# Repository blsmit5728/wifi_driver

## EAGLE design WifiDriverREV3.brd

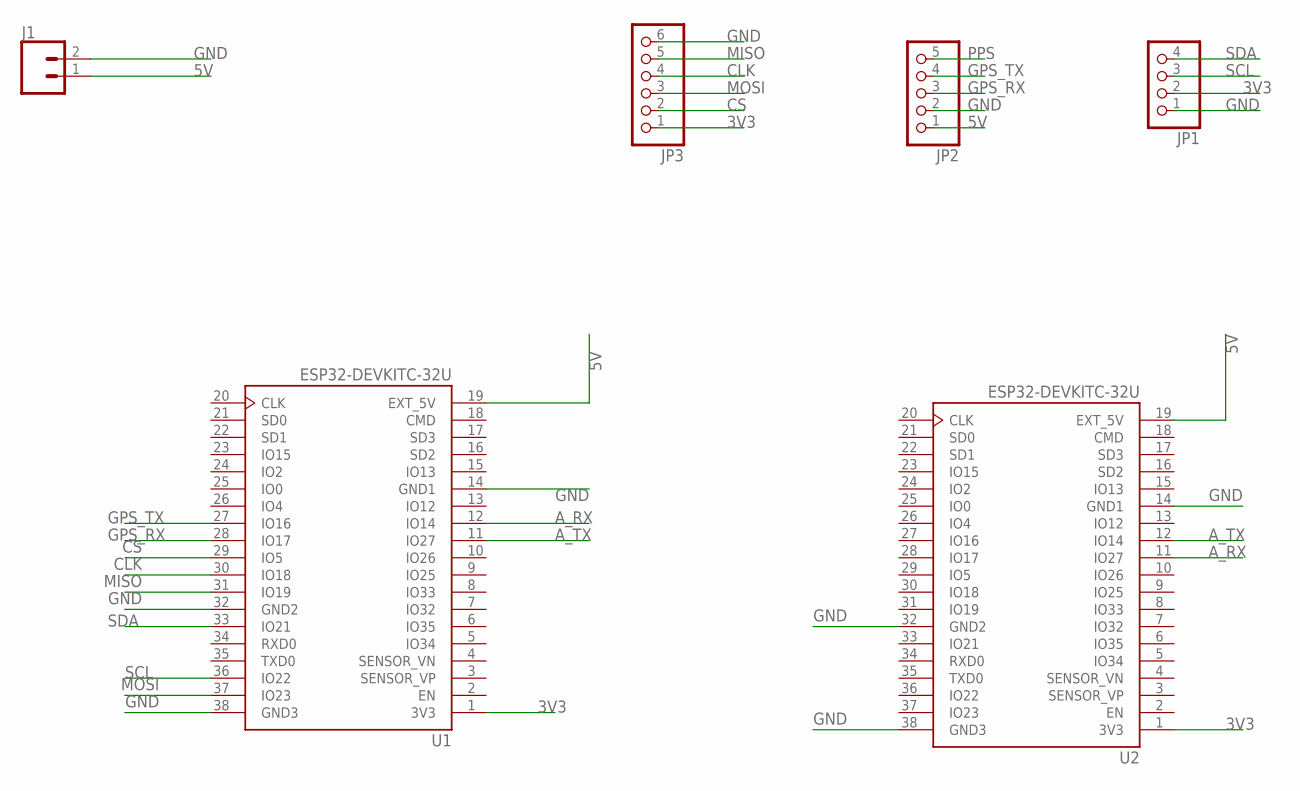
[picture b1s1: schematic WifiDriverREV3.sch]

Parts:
J1: CONN_023.5MM_LOCK; SCREWTERMINAL-3.5MM-2_LOCK
JP1: PINHD-1X4; 1X04
JP2: PINHD-1X5; 1X05
JP3: PINHD-1X6; 1X06
U1, U2: ESP32-DEVKITC-32U; MODULE_ESP32-DEVKITC-32U

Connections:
3V3: JP1.2, JP3.1, U1.1 (3V3), U2.1 (3V3)
5V: J1.1, JP2.1, U1.19 (EXT_5V), U2.19 (EXT_5V)
A_RX: U1.12 (IO14), U2.11 (IO27)
A_TX: U1.11 (IO27), U2.12 (IO14)
CLK: JP3.4, U1.30 (IO18)
CS: JP3.2, U1.29 (IO5)
GND: J1.2, JP1.1, JP2.2, JP3.6, U1.14 (GND1), U1.32 (GND2), U1.38 (GND3), U2.14 (GND1), U2.32 (GND2), U2.38 (GND3)
GPS_RX: JP2.3, U1.28 (IO17)
GPS_TX: JP2.4, U1.27 (IO16)
MISO: JP3.5, U1.31 (IO19)
MOSI: JP3.3, U1.37 (IO23)
PPS: JP2.5
SCL: JP1.3, U1.36 (IO22)
SDA: JP1.4, U1.33 (IO21)

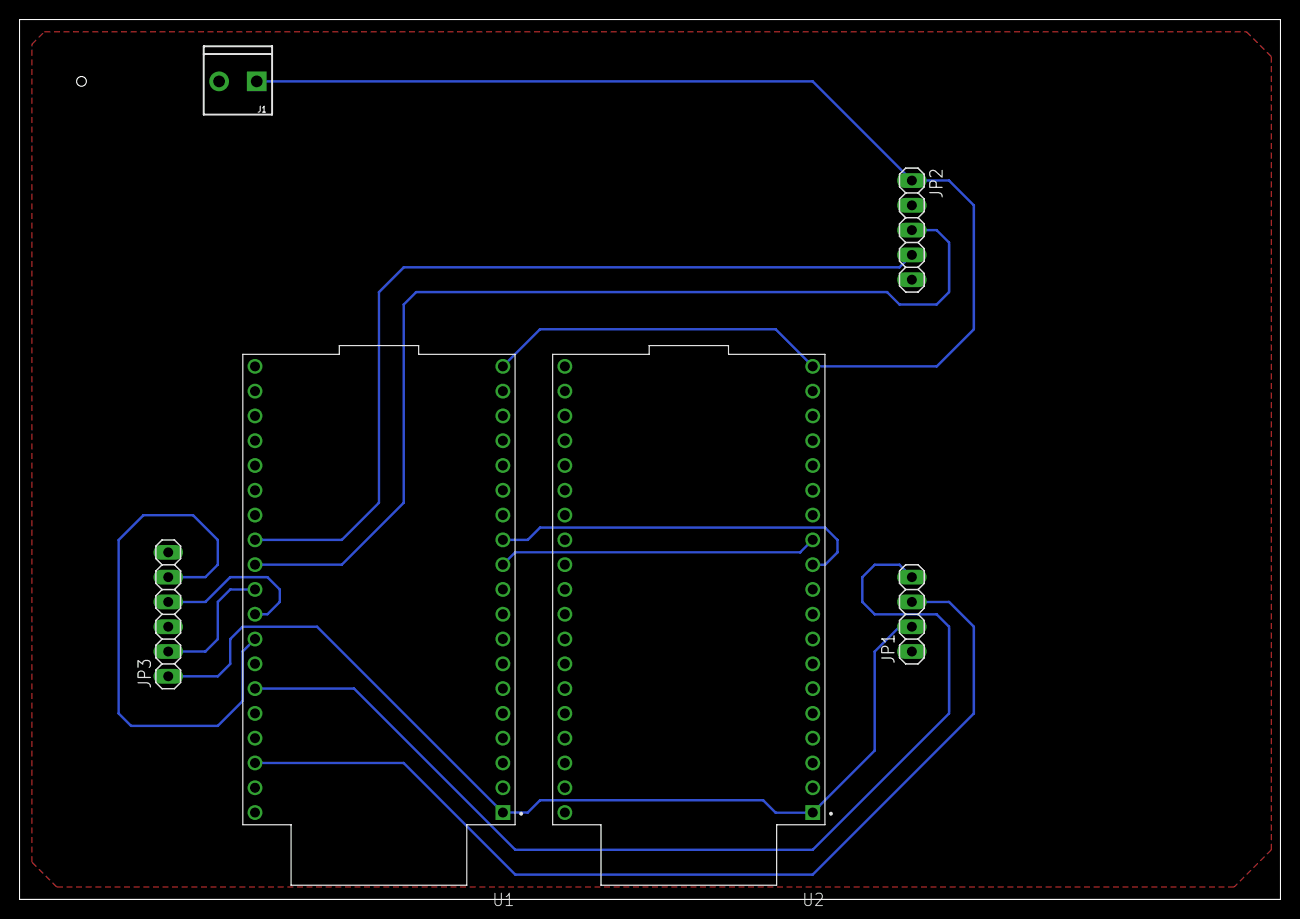
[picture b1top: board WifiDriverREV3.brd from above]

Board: 2 copper layers, 129.2 x 90.2 mm, 6 parts (0 on the bottom side), 13 nets.

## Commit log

2023-05-02 Adding files
2023-05-03 Updated with wardriver_v3 pinout from original author
2023-05-04 rev 2 schematic
2023-05-04 Added ignore
2023-05-23 REV3

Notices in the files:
parts and their libraries:
SparkFun-Connectors: Licensing: Creative Commons ShareAlike 4.0 International - https://creativecommons.org/licenses/by-sa/4.0
